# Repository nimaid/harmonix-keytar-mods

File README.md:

# harmonix-keytar-mods
 Modifications for the Harmonix/Mad Catz Rockband Keytar

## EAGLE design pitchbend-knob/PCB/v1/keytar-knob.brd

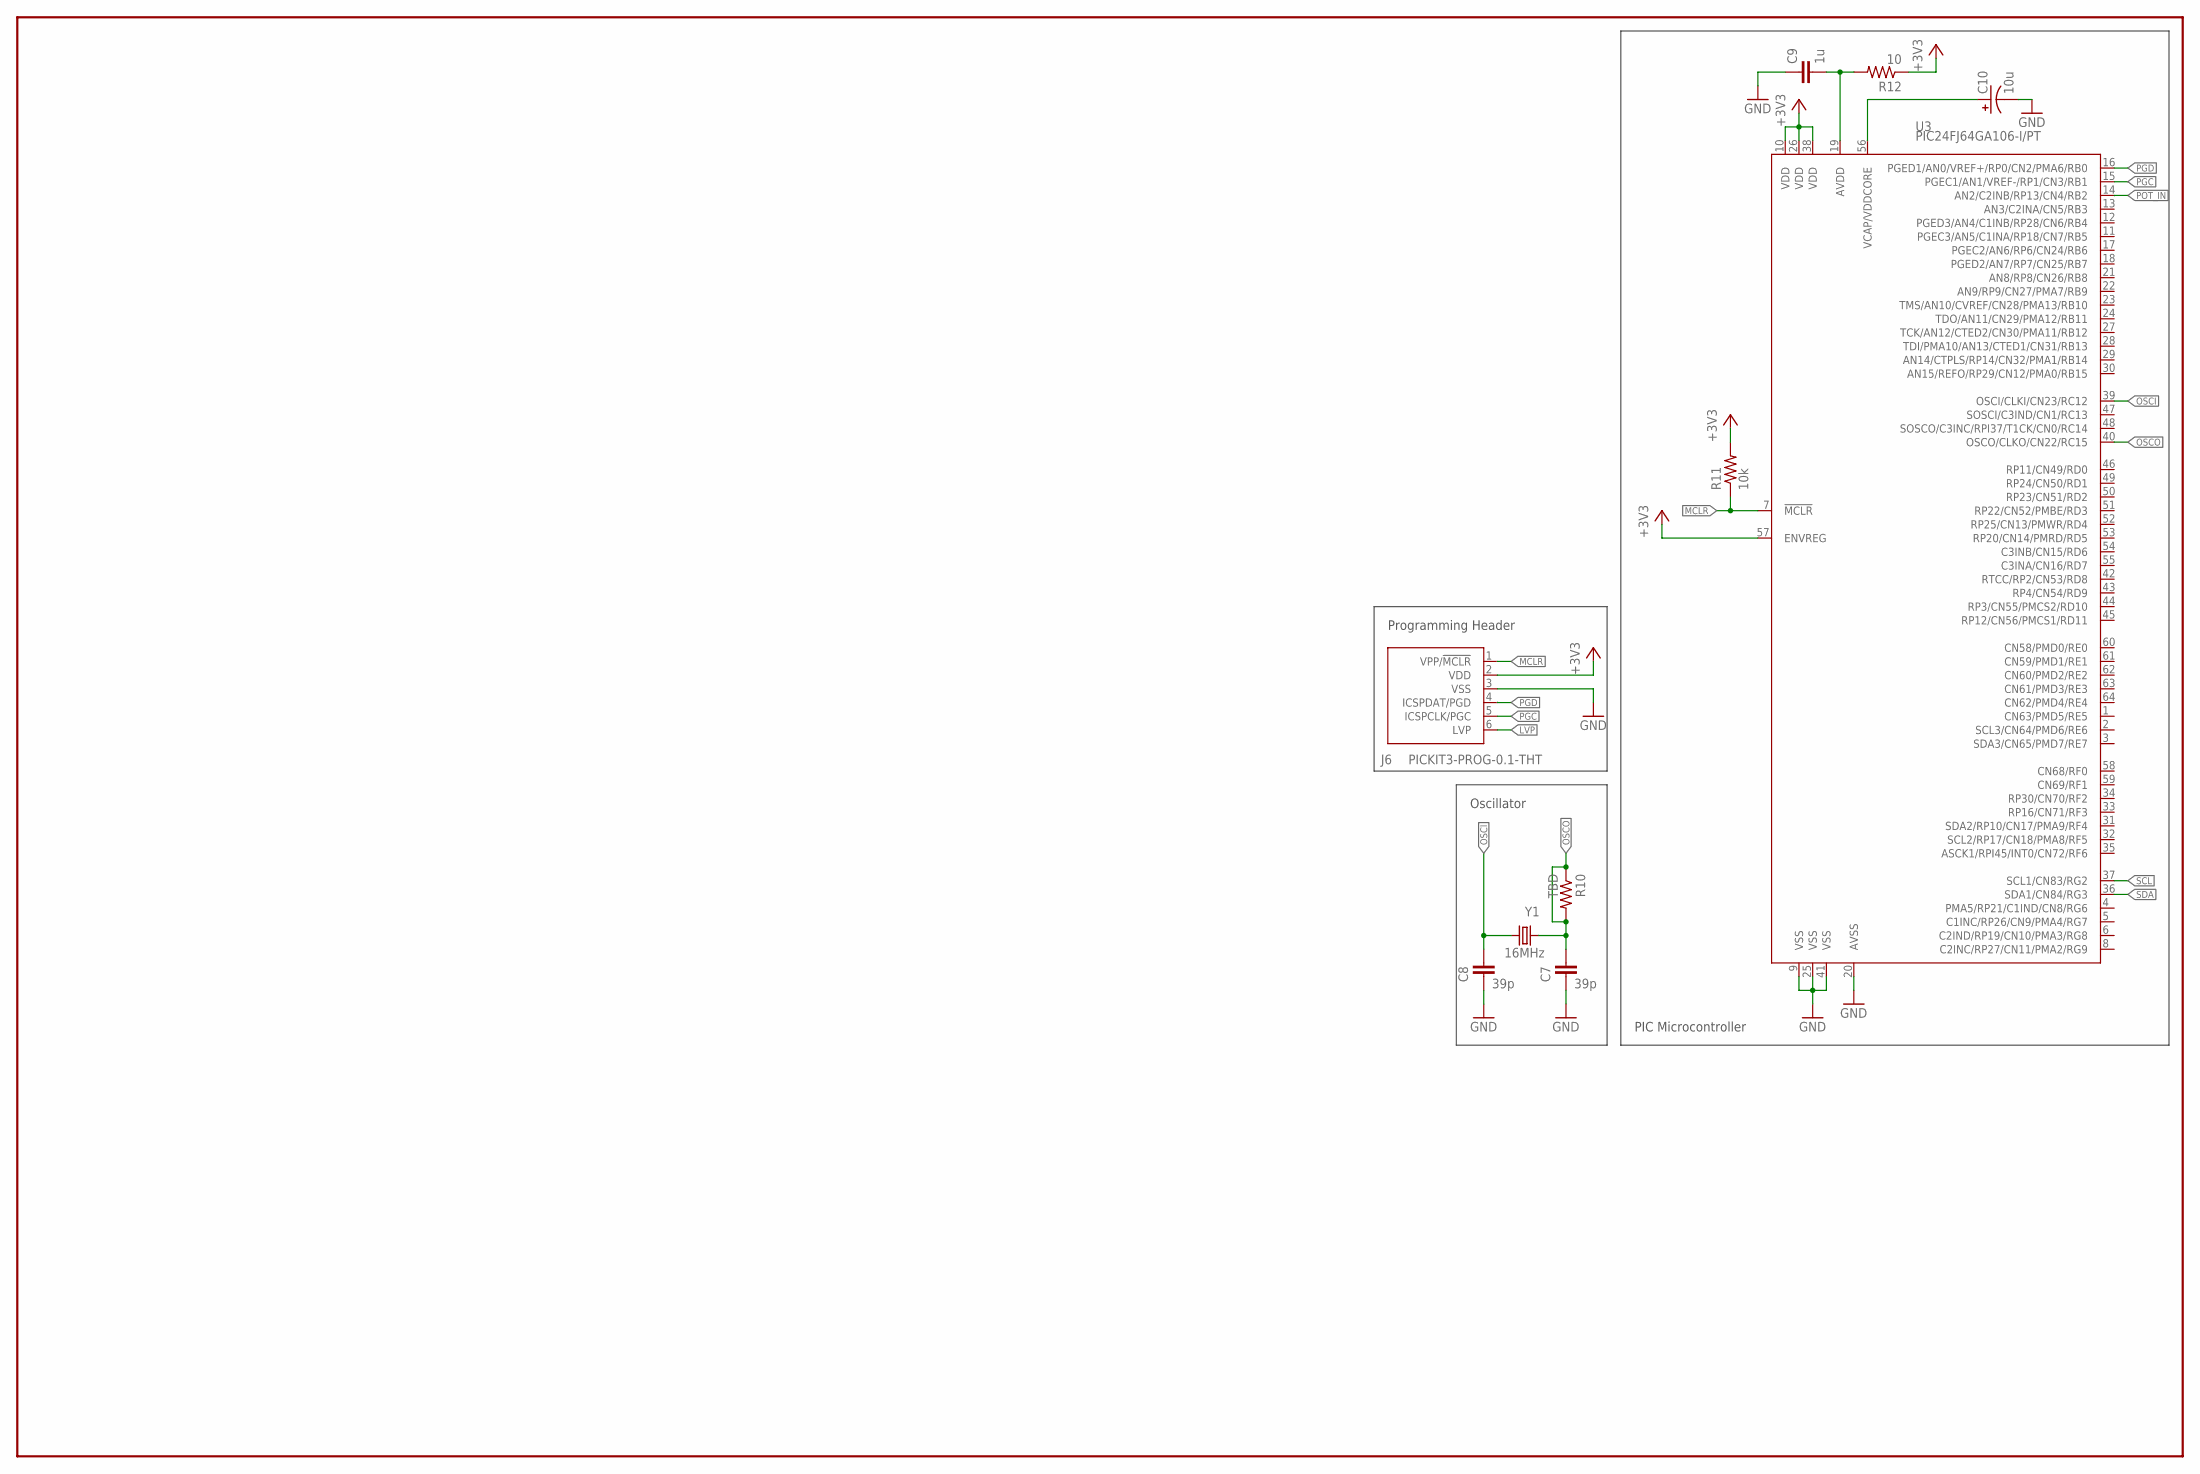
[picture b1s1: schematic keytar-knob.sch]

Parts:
C7, C8: 39p; C0603
C9: 1u; C0603
C10: 10u; AVX-CAP-N
J6: PICKIT3-PROG-0.1-THT; HEADER-0.1-6
R10: TBD; R0603
R11: 10k; R0603
R12: 10; R0603
U3: PIC24FJ64GA106-I/PT; QFP50P1200X1200X120-64N
Y1: 16MHz; CRYSTAL-SMD-4

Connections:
+3V3: J6.2 (VDD), R11.2, R12.1, U3.10 (VDD), U3.26 (VDD), U3.38 (VDD), U3.57 (ENVREG)
GND: C7.2, C8.2, C9.1, C10.C, J6.3 (VSS), U3.9 (VSS), U3.20 (AVSS), U3.25 (VSS), U3.41 (VSS)
LVP: J6.6 (LVP)
MCLR: J6.1 (VPP/!MCLR), R11.1, U3.7 (!MCLR)
unnamed: C9.2, R12.2, U3.19 (AVDD)
unnamed: C10.A, U3.56 (VCAP/VDDCORE)
OSCI: C8.1, U3.39 (OSCI/CLKI/CN23/RC12), Y1.1
OSCO: C7.1, R10.1, R10.2, U3.40 (OSCO/CLKO/CN22/RC15), Y1.3 (2)
PGC: J6.5 (ICSPCLK/PGC), U3.15 (PGEC1/AN1/VREF-/RP1/CN3/RB1)
PGD: J6.4 (ICSPDAT/PGD), U3.16 (PGED1/AN0/VREF+/RP0/CN2/PMA6/RB0)
POT_IN: U3.14 (AN2/C2INB/RP13/CN4/RB2)
SCL: U3.37 (SCL1/CN83/RG2)
SDA: U3.36 (SDA1/CN84/RG3)

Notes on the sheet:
Programming Header
Oscillator
PIC Microcontroller

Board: 2 copper layers, 10 parts (0 on the bottom side), 9 nets, no tracks yet.

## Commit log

2019-10-28 Base code, schematic capture start.
2019-10-28 Added arduino code
